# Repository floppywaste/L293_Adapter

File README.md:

L293_Adapter
============

An adapter circuit board for the L293D motor driver IC. The pin layout is primarily suited to interface a RapberryPi Rev2 using a ribbon cable or so. But any controller with PWM generating ability could be used as well.

The board is two-sided and uses some SMD components.

TODO
====
* Enter part values.
* Document pin layout

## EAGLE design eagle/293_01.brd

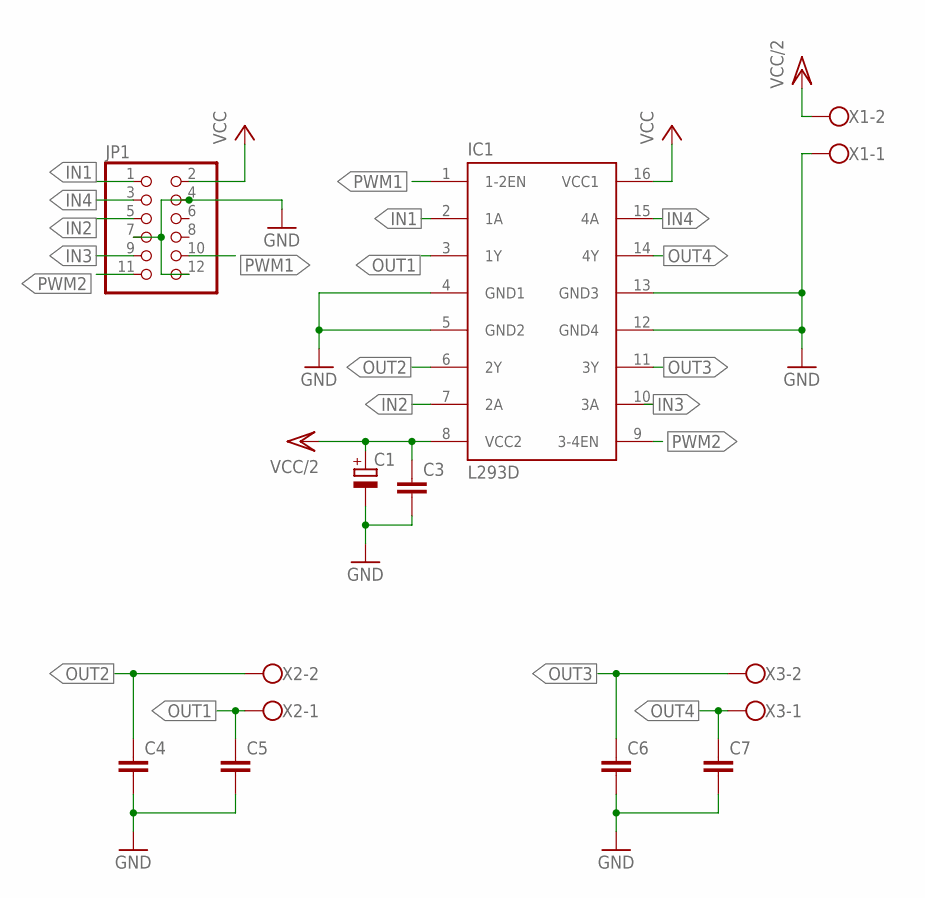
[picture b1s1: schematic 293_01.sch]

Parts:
C1: CPOL-EUE2.5-7; E2,5-7
C3, C4, C5, C6, C7: C-EUC1206; C1206
IC1: L293D; DIL16
JP1: PINHD-2X6; 2X06
X1, X2, X3: W237-102

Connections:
GND: C1.-, C3.2, C4.2, C5.2, C6.2, C7.2, IC1.4 (GND1), IC1.5 (GND2), IC1.12 (GND4), IC1.13 (GND3), JP1.4, JP1.7, JP1.12, X1.1
IN1: IC1.2 (1A), JP1.1
IN2: IC1.7 (2A), JP1.5
IN3: IC1.10 (3A), JP1.9
IN4: IC1.15 (4A), JP1.3
OUT1: C5.1, IC1.3 (1Y), X2.1
OUT2: C4.1, IC1.6 (2Y), X2.2
OUT3: C6.1, IC1.11 (3Y), X3.2
OUT4: C7.1, IC1.14 (4Y), X3.1
PWM1: IC1.1 (1-2EN), JP1.10
PWM2: IC1.9 (3-4EN), JP1.11
VCC: IC1.16 (VCC1), JP1.2
VCC/2: C1.+, C3.1, IC1.8 (VCC2), X1.2

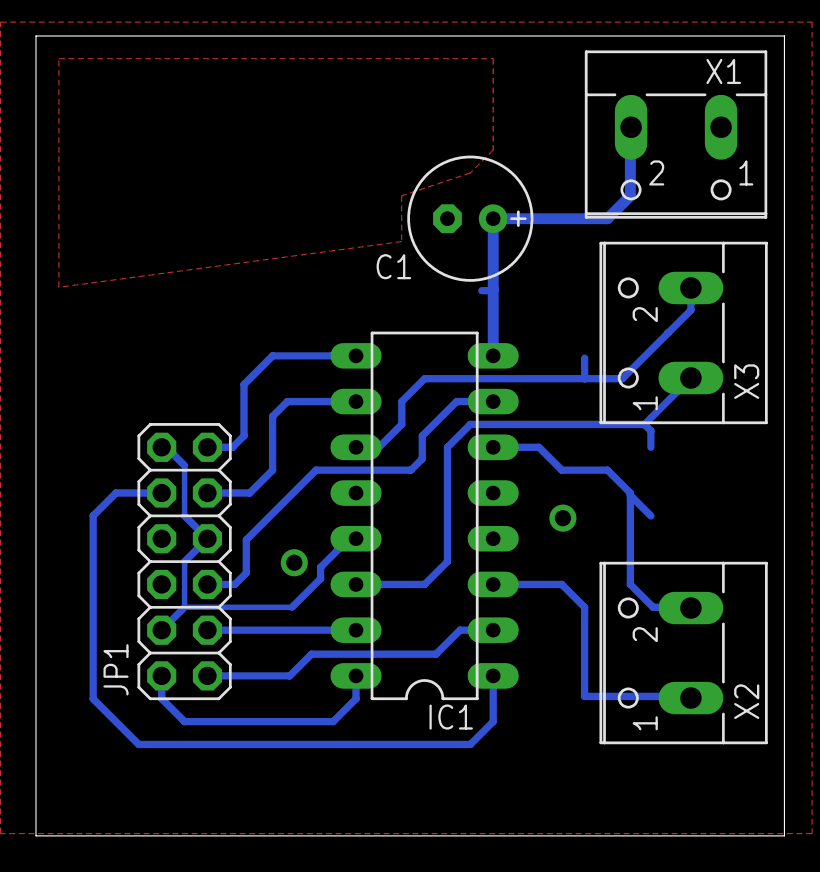
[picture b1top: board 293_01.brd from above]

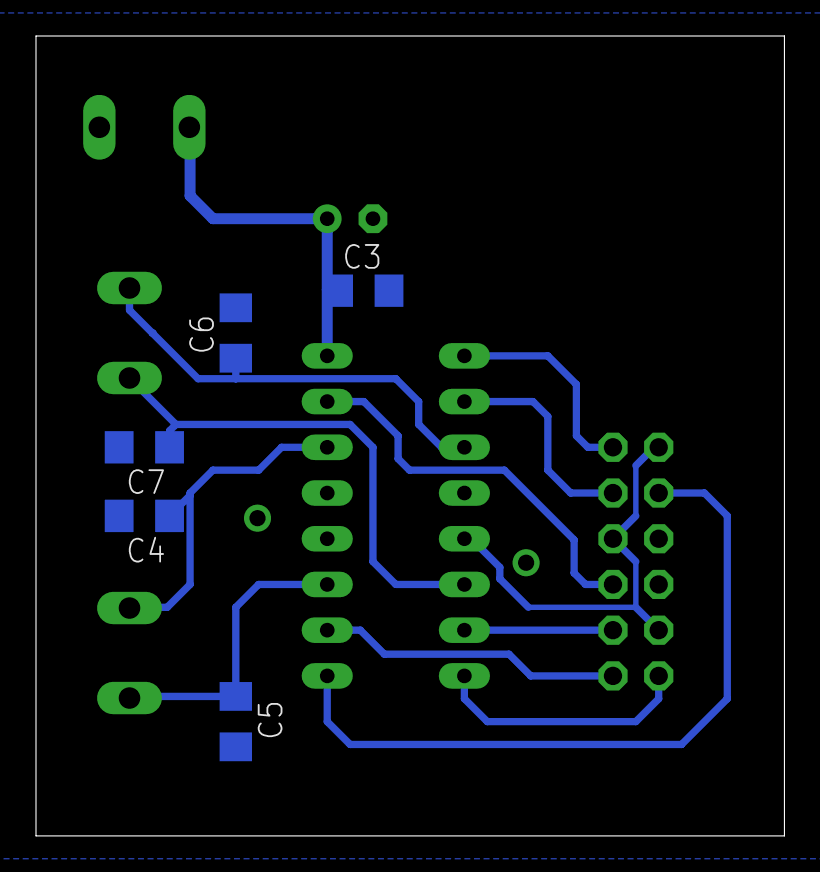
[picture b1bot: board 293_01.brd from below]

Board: 2 copper layers, 41.6 x 44.4 mm, 11 parts (5 on the bottom side), 13 nets.

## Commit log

2014-01-13 eagle files for l293 raspberry adapter
